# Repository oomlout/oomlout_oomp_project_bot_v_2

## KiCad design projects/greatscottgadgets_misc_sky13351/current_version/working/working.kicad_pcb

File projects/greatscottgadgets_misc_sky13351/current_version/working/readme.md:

# misc
 
## summary 
* id: greatscottgadgets_misc_sky13351
* user: greatscottgadgets
* name: misc
* board: sky13351
* repo: https://github.com/greatscottgadgets/misc
* src_file_repo_kicad_pcb: evaluation-boards/sky13351/sky13351.kicad_pcb
* src_file_repo_kicad_pcb_link: https://github.com/greatscottgadgets/misc/tree/master/evaluation-boards/sky13351/sky13351.kicad_pcb
* src_file_repo_kicad_sch: evaluation-boards/Si5351A/Si5351A.kicad_sch
* src_file_repo_kicad_sch_link: https://github.com/greatscottgadgets/misc/tree/master/evaluation-boards/Si5351A/Si5351A.kicad_sch

* src_file_repo_sch: evaluation-boards/sky13351/sky13351.sch
* src_file_repo_sch_link: https://github.com/greatscottgadgets/misc/tree/master/evaluation-boards/sky13351/sky13351.sch
* full details link: https://github.com/oomlout/oomlout_oomp_project_bot_v_2/tree/main/projects/greatscottgadgets_misc_sky13351/current_version/working

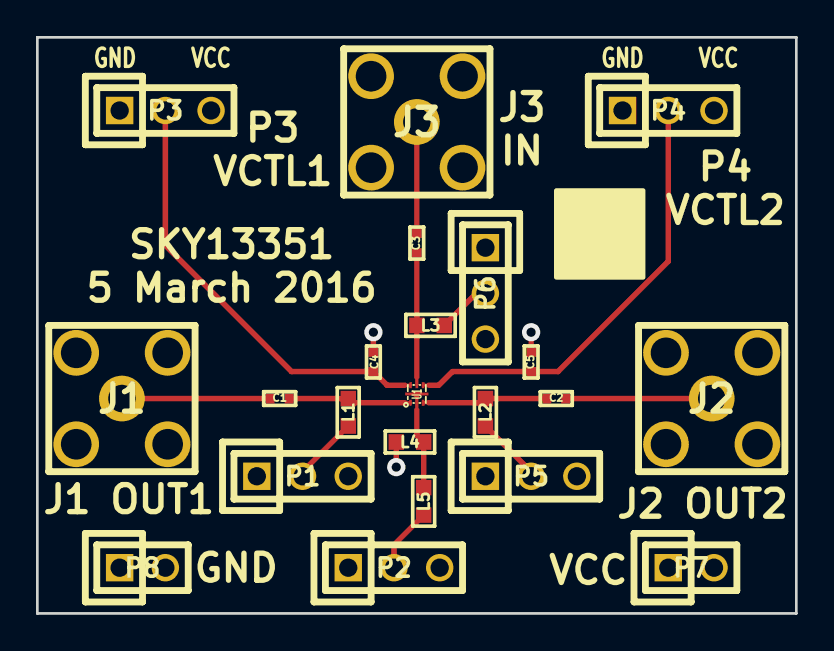
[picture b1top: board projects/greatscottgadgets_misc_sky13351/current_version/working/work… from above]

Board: 4 copper layers, 42.2 x 32.0 mm, 22 parts (0 on the bottom side), 15 nets.

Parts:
C1, C2, C3: 100nF; 0402
C4, C5: 33pF; 0402
J1, J2, J3: SMA; SMA-VERTICAL
L1, L2, L3, L4, L5: 15uH; 0603
P1, P2, P3, P4, P5, P6: CONN_01X03; HEADER-1x3
P7, P8: CONN_01X02; HEADER-1x2
U1: SKY13351; SKY13351-378LF

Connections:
GND: C4.2, C5.1, J1.2, J2.2, J3.2, L4.1, P1.1, P2.1, P3.1, P4.1, P5.1, P6.1, P8.1, P8.2
unnamed: C1.1, L1.2, U1.1
unnamed: C1.2, J1.1
unnamed: C2.1, J2.1
unnamed: C2.2, L2.2, U1.3
unnamed: C3.1, J3.1
unnamed: C3.2, L3.2, U1.5
unnamed: C4.1, P3.2, U1.6
unnamed: C5.2, P4.2, U1.4
unnamed: L1.1, P1.2
unnamed: L2.1, P5.2
unnamed: L3.1, P6.2
unnamed: L4.2, L5.2, U1.2
unnamed: L5.1, P2.2
VCC: P1.3, P2.3, P3.3, P4.3, P5.3, P6.3, P7.1, P7.2

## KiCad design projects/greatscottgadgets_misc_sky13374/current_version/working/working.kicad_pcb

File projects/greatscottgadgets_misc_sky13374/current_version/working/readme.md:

# misc
 
## summary 
* id: greatscottgadgets_misc_sky13374
* user: greatscottgadgets
* name: misc
* board: sky13374
* repo: https://github.com/greatscottgadgets/misc
* src_file_repo_kicad_pcb: evaluation-boards/sky13374/sky13374.kicad_pcb
* src_file_repo_kicad_pcb_link: https://github.com/greatscottgadgets/misc/tree/master/evaluation-boards/sky13374/sky13374.kicad_pcb
* src_file_repo_kicad_sch: evaluation-boards/Si5351A/Si5351A.kicad_sch
* src_file_repo_kicad_sch_link: https://github.com/greatscottgadgets/misc/tree/master/evaluation-boards/Si5351A/Si5351A.kicad_sch

* src_file_repo_sch: evaluation-boards/sky13374/sky13374.sch
* src_file_repo_sch_link: https://github.com/greatscottgadgets/misc/tree/master/evaluation-boards/sky13374/sky13374.sch
* full details link: https://github.com/oomlout/oomlout_oomp_project_bot_v_2/tree/main/projects/greatscottgadgets_misc_sky13374/current_version/working

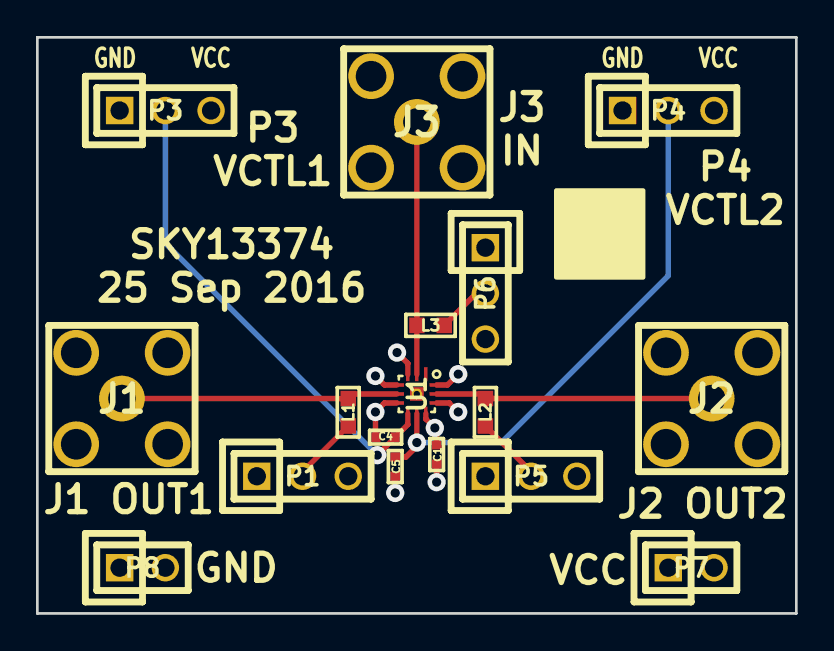
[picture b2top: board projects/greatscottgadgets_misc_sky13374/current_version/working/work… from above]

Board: 4 copper layers, 42.2 x 32.0 mm, 17 parts (0 on the bottom side), 10 nets.

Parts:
C1: 100nF; 0402
C4, C5: 33pF; 0402
J1, J2, J3: SMA; SMA-VERTICAL
L1, L2, L3: 15uH; 0603
P1, P3, P4, P5, P6: CONN_01X03; HEADER-1x3
P7, P8: CONN_01X02; HEADER-1x2
U1: SKY13374; SKY13374-397LF

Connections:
GND: C1.1, C4.2, C5.1, J1.2, J2.2, J3.2, P1.1, P3.1, P4.1, P5.1, P6.1, P8.1, P8.2, U1.0, U1.3, U1.4, U1.6, U1.10, U1.12
unnamed: C4.1, P3.2, U1.7
unnamed: C5.2, P4.2, U1.8
unnamed: J1.1, L1.2, U1.5
unnamed: J2.1, L2.2, U1.11
unnamed: J3.1, L3.2, U1.2
unnamed: L1.1, P1.2
unnamed: L2.1, P5.2
unnamed: L3.1, P6.2
VCC: C1.2, P1.3, P3.3, P4.3, P5.3, P6.3, P7.1, P7.2, U1.9

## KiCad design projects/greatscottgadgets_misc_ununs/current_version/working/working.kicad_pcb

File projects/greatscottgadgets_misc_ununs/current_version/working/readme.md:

# misc
 
## summary 
* id: greatscottgadgets_misc_ununs
* user: greatscottgadgets
* name: misc
* board: ununs
* repo: https://github.com/greatscottgadgets/misc
* src_file_repo_kicad_pcb: evaluation-boards/ununs/ununs.kicad_pcb
* src_file_repo_kicad_pcb_link: https://github.com/greatscottgadgets/misc/tree/master/evaluation-boards/ununs/ununs.kicad_pcb
* src_file_repo_kicad_sch: evaluation-boards/ununs/ununs.kicad_sch
* src_file_repo_kicad_sch_link: https://github.com/greatscottgadgets/misc/tree/master/evaluation-boards/ununs/ununs.kicad_sch

* src_file_repo_sch: evaluation-boards/ununs/ununs.sch
* src_file_repo_sch_link: https://github.com/greatscottgadgets/misc/tree/master/evaluation-boards/ununs/ununs.sch
* full details link: https://github.com/oomlout/oomlout_oomp_project_bot_v_2/tree/main/projects/greatscottgadgets_misc_ununs/current_version/working

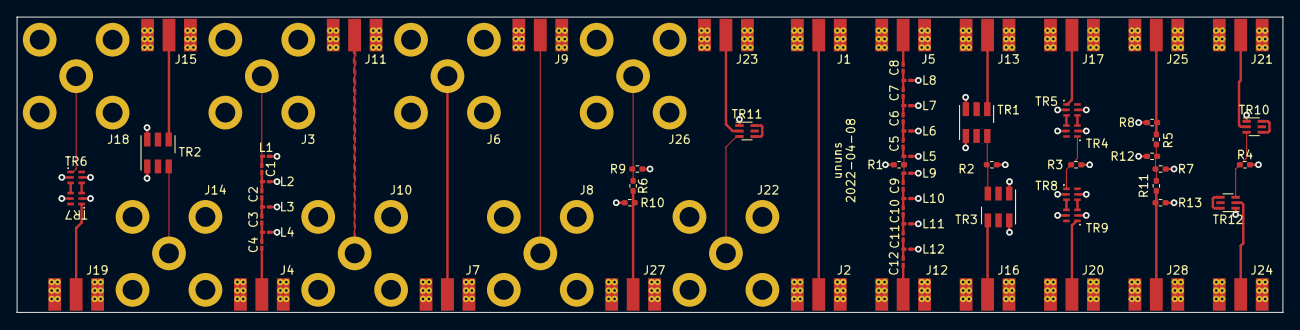
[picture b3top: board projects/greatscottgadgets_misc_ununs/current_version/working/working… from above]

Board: 4 copper layers, 150.0 x 35.0 mm, 77 parts (0 on the bottom side), 48 nets.

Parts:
C1, C5, C9: 3.9 pF; C_0201_0603Metric_Pad0.64x0.40mm_HandSolder
C2, C6, C10: 3.3 pF; C_0201_0603Metric_Pad0.64x0.40mm_HandSolder
C3, C7, C11: 15 pF; C_0201_0603Metric_Pad0.64x0.40mm_HandSolder
C4, C8, C12: 5.1 pF; C_0201_0603Metric_Pad0.64x0.40mm_HandSolder
J1, J2, J4, J5, J7, J9, J11, J12, J13, J15, J16, J17, J19, J20, J21, J23, J24, J25, J27, J28: Conn_Coaxial; SMA-EDGE
J3, J6, J8, J10, J14, J18, J22, J26: Conn_Coaxial; F_Cinch_VF320_Vertical
L1, L5, L9: 16 nH; L_0201_0603Metric_Pad0.64x0.40mm_HandSolder
L2, L6, L10: 20 nH; L_0201_0603Metric_Pad0.64x0.40mm_HandSolder
L3, L7, L11: 12 nH; L_0201_0603Metric_Pad0.64x0.40mm_HandSolder
L4, L8, L12: 22 nH; L_0201_0603Metric_Pad0.64x0.40mm_HandSolder
R1, R2, R3, R4: 75; R_0402_1005Metric_Pad0.72x0.64mm_HandSolder
R5, R6, R11: 43.2; R_0402_1005Metric_Pad0.72x0.64mm_HandSolder
R7, R9, R12: R; R_0402_1005Metric_Pad0.72x0.64mm_HandSolder
R8, R10, R13: 86.6; R_0402_1005Metric_Pad0.72x0.64mm_HandSolder
TR1, TR2, TR3: TC1.5-1+; Mini-Circuits_DB1627
TR4, TR6, TR8: HHM15112A1
TR5, TR7, TR9: 1720BL15A0100E; HHM15112A1
TR10, TR11, TR12: 1350BL15B0075; Balun_Johanson_0896BM15A0001

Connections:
GND: J1.2 (Ext), J2.2 (Ext), J3.2 (Ext), J4.2 (Ext), J5.2 (Ext), J6.2 (Ext), J7.2 (Ext), J8.2 (Ext), J9.2 (Ext), J10.2 (Ext), J11.2 (Ext), J12.2 (Ext), J13.2 (Ext), J14.2 (Ext), J15.2 (Ext), J16.2 (Ext), J17.2 (Ext), J18.2 (Ext), J19.2 (Ext), J20.2 (Ext), J21.2 (Ext), J22.2 (Ext), J23.2 (Ext), J24.2 (Ext), J25.2 (Ext), J26.2 (Ext), J27.2 (Ext), J28.2 (Ext), L1.2, L2.2, L3.2, L4.2, L5.2, L6.2, L7.2, L8.2, L9.2, L10.2, L11.2, L12.2, R1.2, R2.2, R3.2, R4.2, R7.2, R8.1, R9.2, R10.1, R12.2, R13.1, TR1.3, TR1.4, TR2.3, TR2.4, TR3.3, TR3.4, TR4.2, TR4.5, TR5.2, TR5.5, TR6.2, TR6.5, TR7.2, TR7.5, TR8.2, TR8.5, TR9.2, TR9.5, TR10.1, TR11.1, TR12.1
unnamed: C1.1, J3.1 (In), L1.1
unnamed: C1.2, C2.1, L2.1
unnamed: C2.2, C3.1, L3.1
unnamed: C3.2, C4.1, L4.1
unnamed: C4.2, J4.1 (In)
unnamed: C5.1, C9.1, L5.1, L9.1, R1.1
unnamed: C5.2, C6.1, L6.1
unnamed: C6.2, C7.1, L7.1
unnamed: C7.2, C8.1, L8.1
unnamed: C8.2, J5.1 (In)
unnamed: C9.2, C10.1, L10.1
unnamed: C10.2, C11.1, L11.1
unnamed: C11.2, C12.1, L12.1
unnamed: C12.2, J12.1 (In)
unnamed: J1.1 (In), J2.1 (In)
unnamed: J6.1 (In), J7.1 (In)
unnamed: J8.1 (In), J9.1 (In)
unnamed: J10.1 (In), J11.1 (In)
unnamed: J13.1 (In), TR1.6
unnamed: J14.1 (In), TR2.1
unnamed: J15.1 (In), TR2.6
unnamed: J16.1 (In), TR3.6
unnamed: J17.1 (In), TR5.1
unnamed: J18.1 (In), TR6.1
unnamed: J19.1 (In), TR7.1
unnamed: J20.1 (In), TR9.1
unnamed: J21.1 (In), TR10.2
unnamed: J22.1 (In), TR11.3
unnamed: J23.1 (In), TR11.2
unnamed: J24.1 (In), TR12.2
unnamed: J25.1 (In), R5.2, R8.2
unnamed: J26.1 (In), R6.1, R9.1
unnamed: J27.1 (In), R6.2, R10.2
unnamed: J28.1 (In), R11.2, R13.2
unnamed: R2.1, TR1.1, TR3.1
unnamed: R3.1, TR4.1, TR8.1
unnamed: R4.1, TR10.3, TR12.3
unnamed: R5.1, R7.1, R11.1, R12.1
unnamed: TR4.3, TR5.4
unnamed: TR4.4, TR5.3
unnamed: TR6.3, TR7.4
unnamed: TR6.4, TR7.3
unnamed: TR8.3, TR9.4
unnamed: TR8.4, TR9.3
unnamed: TR10.4, TR10.6
unnamed: TR11.4, TR11.6
unnamed: TR12.4, TR12.6

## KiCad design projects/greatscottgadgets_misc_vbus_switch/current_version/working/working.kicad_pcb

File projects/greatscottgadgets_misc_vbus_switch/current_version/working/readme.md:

# misc
 
## summary 
* id: greatscottgadgets_misc_vbus_switch
* user: greatscottgadgets
* name: misc
* board: vbus_switch
* repo: https://github.com/greatscottgadgets/misc
* src_file_repo_kicad_pcb: evaluation-boards/vbus-switch/vbus-switch.kicad_pcb
* src_file_repo_kicad_pcb_link: https://github.com/greatscottgadgets/misc/tree/master/evaluation-boards/vbus-switch/vbus-switch.kicad_pcb
* src_file_repo_kicad_sch: evaluation-boards/vbus-switch/vbus-switch.kicad_sch
* src_file_repo_kicad_sch_link: https://github.com/greatscottgadgets/misc/tree/master/evaluation-boards/vbus-switch/vbus-switch.kicad_sch

* src_file_repo_sch: evaluation-boards/ununs/ununs.sch
* src_file_repo_sch_link: https://github.com/greatscottgadgets/misc/tree/master/evaluation-boards/ununs/ununs.sch
* full details link: https://github.com/oomlout/oomlout_oomp_project_bot_v_2/tree/main/projects/greatscottgadgets_misc_vbus_switch/current_version/working

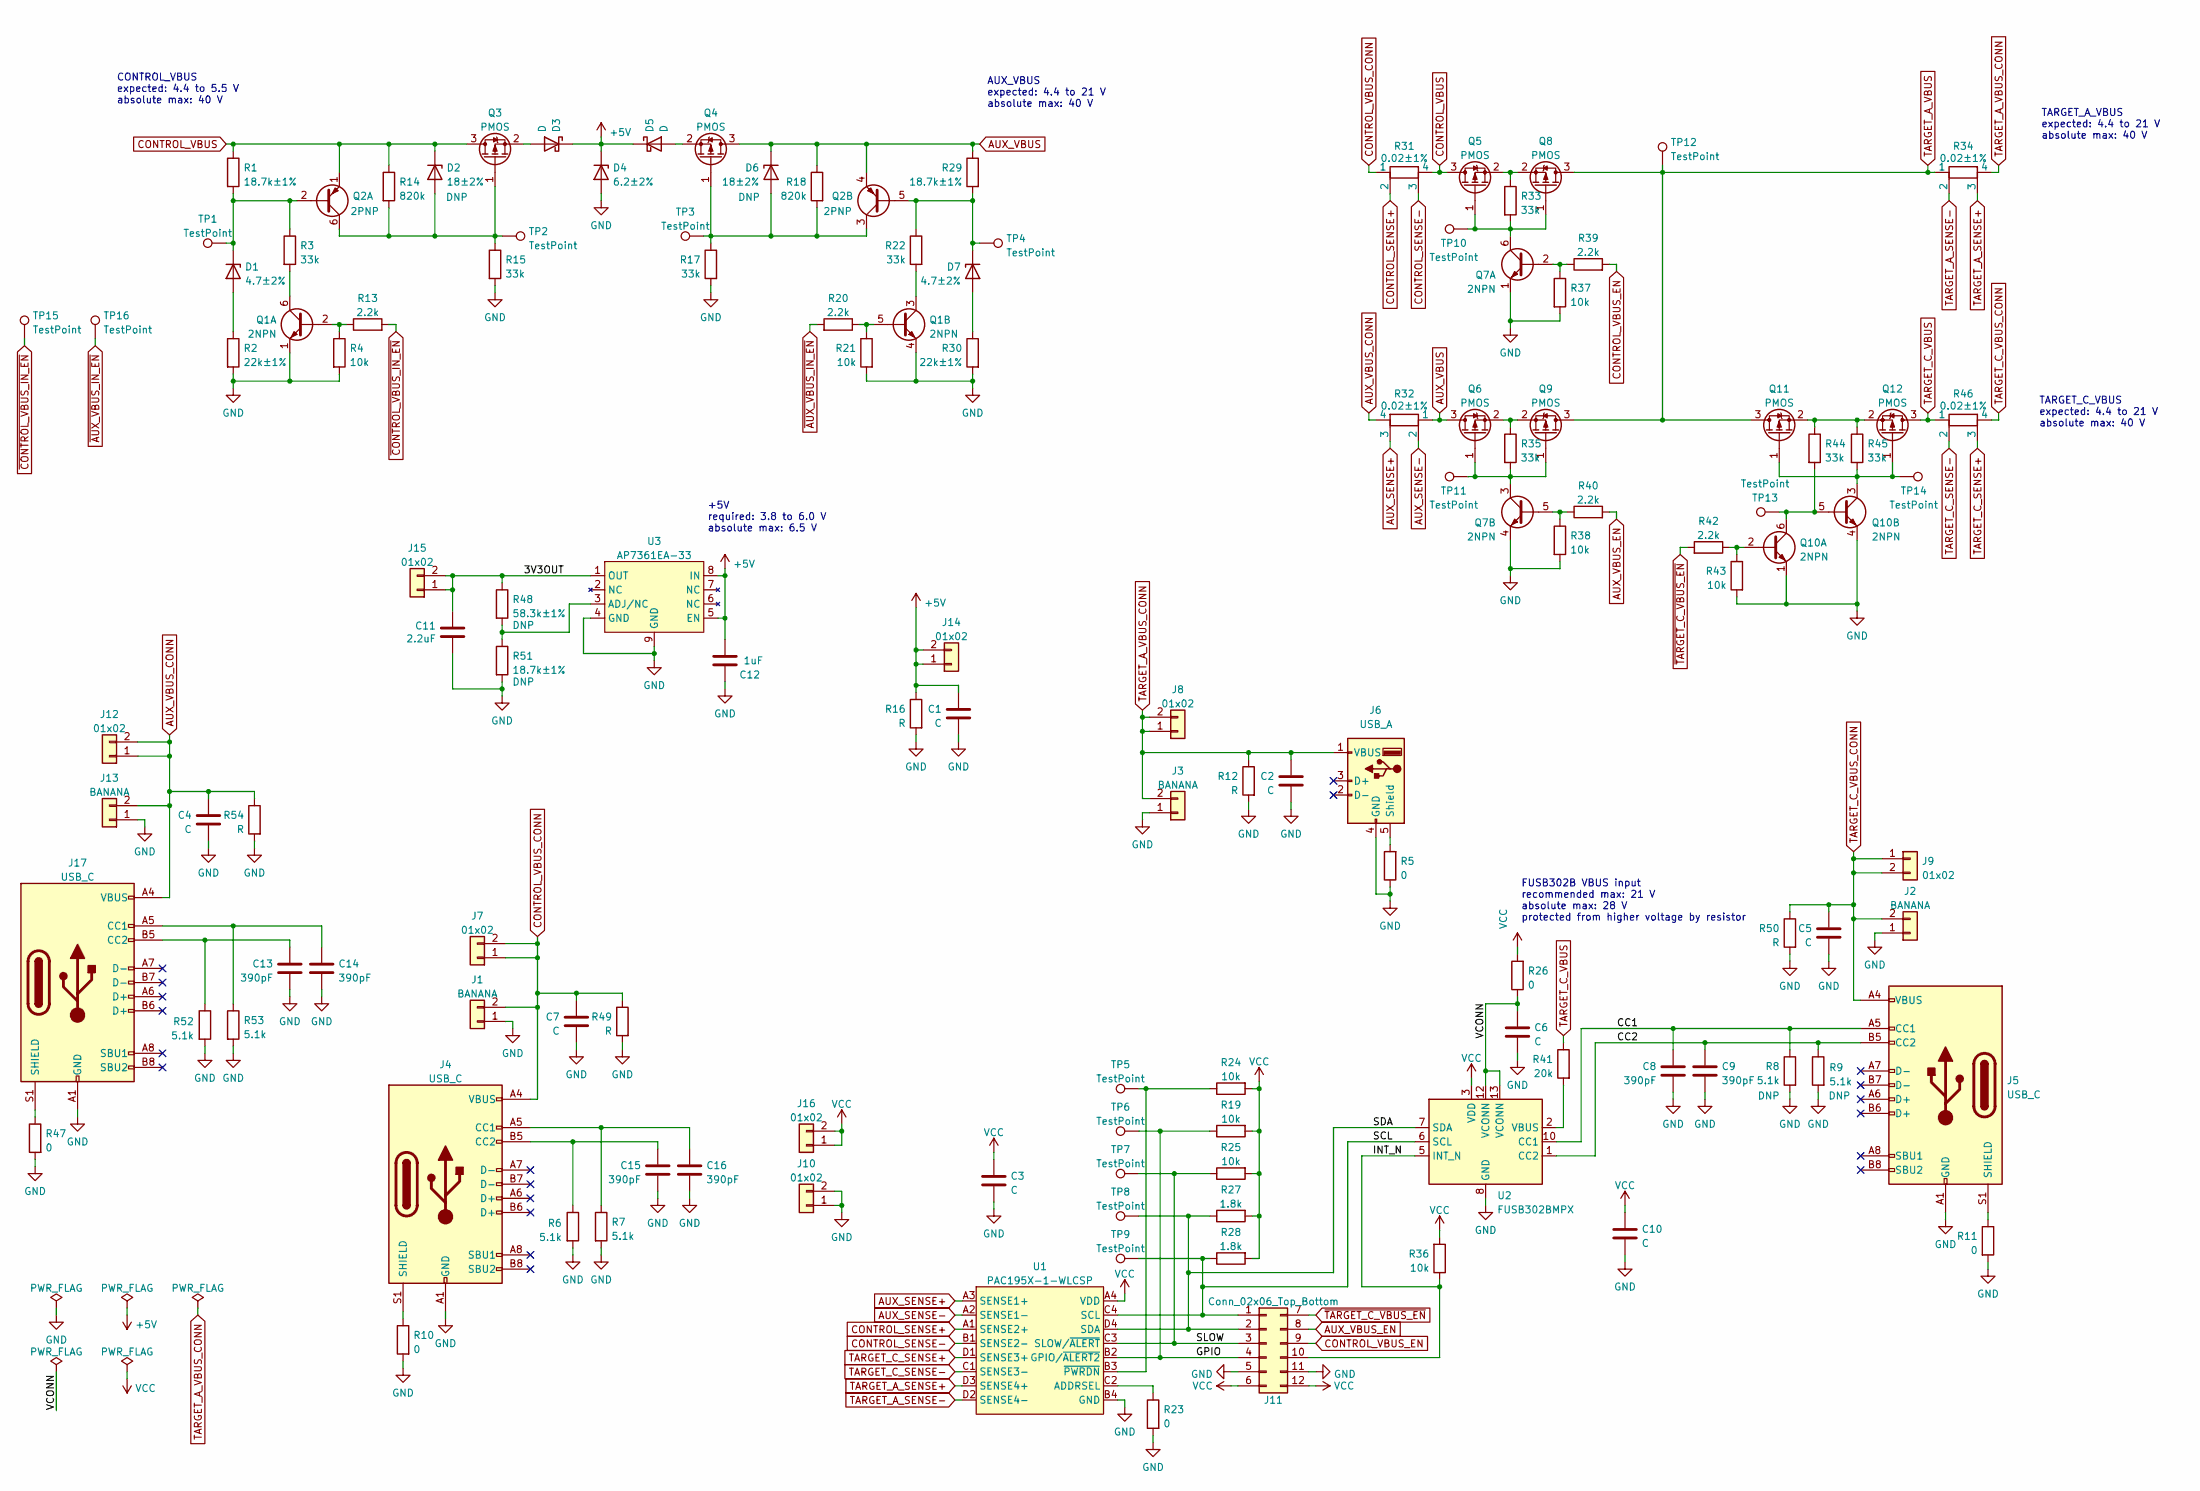
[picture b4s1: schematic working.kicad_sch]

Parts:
C1, C2, C3, C4, C5, C6, C7, C10: C; C_0402_1005Metric
C8, C9, C13, C14, C15, C16: 390pF; C_0402_1005Metric
C11: 2.2uF; C_0603_1608Metric; Part Number CL10A225KP8NNNC
C12: 1uF; C_0603_1608Metric; Part Number GENERIC-CAP-0603-1uF
D1, D7: 4.7±2%; DFN1006-2; Part Number BZX884-B4V7,315
D2, D6: 18±2%; DFN1006-2; Part Number BZX884-B18,315
D3, D5: D; D_SOD-123F; Part Number PMEG10010ELRX
D4: 6.2±2%; DFN1006-2; Part Number BZX884-B6V2,315
J1, J2, J3, J13: BANANA; Banana_Jack_2Pin
J4, J5, J17: USB_C; USB_C_Receptacle_HRO_TYPE-C-31-M-12; Part Number U262-161N-4BVC11
J6: USB_A; USB_A_Kycon_KUSBXHT-SB-AS1N-B30-NF_Horizontal; Part Number C42411
J7, J8, J9, J10, J12, J14, J15, J16: 01x02; PinHeader_1x02_P2.54mm_Vertical
J11: Conn_02x06_Top_Bottom; PinHeader_2x06_P2.54mm_PMOD
Q1, Q7, Q10: 2NPN; SOT-363_SC-70-6; Part Number BC847BS
Q2: 2PNP; SOT-363_SC-70-6; Part Number BCM857BS
Q3, Q4, Q5, Q6, Q8, Q9, Q11, Q12: PMOS; SOT-23-3; Part Number PJA3441_R1_00001
R1, R29, R51: 18.7k±1%; R_0402_1005Metric
R2, R30: 22k±1%; R_0402_1005Metric
R3, R15, R17, R22, R33, R35, R44, R45: 33k; R_0402_1005Metric
R4, R19, R21, R24, R25, R36, R37, R38, R43: 10k; R_0402_1005Metric
R5, R10, R11, R23, R26, R47: 0; R_0402_1005Metric
R6, R7, R8, R9, R52, R53: 5.1k; R_0402_1005Metric
R12, R16, R49, R50, R54: R; R_0402_1005Metric
R13, R20, R39, R40, R42: 2.2k; R_0402_1005Metric
R14, R18: 820k; R_0402_1005Metric
R27, R28: 1.8k; R_0402_1005Metric
R31, R32, R34, R46: 0.02±1%; R_0603_1608Metric_Current_Sense; Part Number ERJ-3BWFR020V
R41: 20k; R_0402_1005Metric
R48: 58.3k±1%; R_0402_1005Metric
TP1, TP2, TP3, TP4, TP5, TP6, TP7, TP8, TP9, TP10, TP11, TP12, TP13, TP14, TP15, TP16: TestPoint; TestPoint_Pad_D1.5mm
U1: PAC195X-1-WLCSP; WLCSP-16_2.225x2.170mm_Layout4x4_P0.5mm; Part Number PAC1954T-E/J6CX
U2: FUSB302BMPX; WQFN-14-1EP_2.5x2.5mm_P0.5mm_EP1.45x1.45mm; Part Number FUSB302BMPX
U3: AP7361EA-33; DFN-8-1EP_3x3mm_P0.65mm_EP1.55x2.4mm; Part Number AP7361EA-33FGE-7

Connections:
+5V: C1.1, C12.2, D3.1 (K), D4.1 (K), D5.1 (K), J14.1, J14.2, R16.1, U3.5 (EN), U3.8 (IN)
/3V3OUT: C11.1, J15.1, J15.2, R48.1, U3.1 (OUT)
/CC1: C8.2, J5.A5 (CC1), R8.1, U2.10 (CC1), U2.11 (CC1)
/CC2: C9.1, J5.B5 (CC2), R9.1, U2.1 (CC2), U2.14 (CC2)
/GPIO: J11.4, R19.1, TP6.1, U1.B2 (GPIO/~ALERT2)
/INT_N: J11.10, R36.1, U2.5 (INT_N)
/SCL: J11.1, R28.1, TP9.1, U1.C4 (SCL), U2.6 (SCL)
/SDA: J11.2, R27.1, TP8.1, U1.D4 (SDA), U2.7 (SDA)
/SLOW: J11.3, R25.1, TP7.1, U1.C3 (SLOW/~ALERT)
/VCONN: C6.1, R26.1, U2.12 (VCONN), U2.13 (VCONN)
AUX_SENSE+: R32.3, U1.A3 (SENSE1+)
AUX_SENSE-: R32.2, U1.A2 (SENSE1-)
AUX_VBUS: D6.1 (K), Q2.4 (E2), Q4.3 (D), Q6.3 (D), R18.1, R29.1, R32.1
AUX_VBUS_CONN: C4.1, J12.1, J12.2, J13.2, J17.A4 (VBUS), J17.A9 (VBUS), J17.B4 (VBUS), J17.B9 (VBUS), R32.4, R54.1
AUX_VBUS_EN: J11.8, R40.2
CONTROL_SENSE+: R31.2, U1.A1 (SENSE2+)
CONTROL_SENSE-: R31.3, U1.B1 (SENSE2-)
CONTROL_VBUS: D2.1 (K), Q2.1 (E1), Q3.3 (D), Q5.3 (D), R1.1, R14.1, R31.4
CONTROL_VBUS_CONN: C7.1, J1.2, J4.A4 (VBUS), J4.A9 (VBUS), J4.B4 (VBUS), J4.B9 (VBUS), J7.1, J7.2, R31.1, R49.1
CONTROL_VBUS_EN: J11.9, R39.2
GND: C1.2, C2.2, C3.2, C4.2, C5.2, C6.2, C7.2, C8.1, C9.2, C10.2, C11.2, C12.1, C13.1, C14.2, C15.1, C16.2, D4.2 (A), J1.1, J2.1, J3.1, J4.A1 (GND), J4.A12 (GND), J4.B1 (GND), J4.B12 (GND), J5.A1 (GND), J5.A12 (GND), J5.B1 (GND), J5.B12 (GND), J6.4 (GND), J10.1, J10.2, J11.5, J11.11, J13.1, J17.A1 (GND), J17.A12 (GND), J17.B1 (GND), J17.B12 (GND), Q1.1 (E1), Q1.4 (E2), Q7.1 (E1), Q7.4 (E2), Q10.1 (E1), Q10.4 (E2), R2.2, R4.2, R5.1, R6.2, R7.2, R8.2, R9.2, R10.2, R11.2, R12.2, R15.2, R16.2, R17.2, R21.2, R23.2, R30.2, R37.2, R38.2, R43.2, R47.2, R49.2, R50.2, R51.2, R52.2, R53.2, R54.2, U1.B4 (GND), U2.8 (GND), U2.9 (GND), U2.15 (GND), U3.4 (GND), U3.9 (GND)
unnamed: C13.2, J17.B5 (CC2), R52.1
unnamed: C14.1, J17.A5 (CC1), R53.1
unnamed: C15.2, J4.B5 (CC2), R6.1
unnamed: C16.1, J4.A5 (CC1), R7.1
unnamed: D1.1 (K), Q2.2 (B1), R1.2, R3.1, TP1.1
unnamed: D1.2 (A), R2.1
unnamed: D2.2 (A), Q2.6 (C1), Q3.1 (G), R14.2, R15.1, TP2.1
unnamed: D3.2 (A), Q3.2 (S)
unnamed: D5.2 (A), Q4.2 (S)
unnamed: D6.2 (A), Q2.3 (C2), Q4.1 (G), R17.1, R18.2, TP3.1
unnamed: D7.1 (K), Q2.5 (B2), R22.1, R29.2, TP4.1
unnamed: D7.2 (A), R30.1
unnamed: J4.S1 (SHIELD), R10.1
unnamed: J5.S1 (SHIELD), R11.1
unnamed: J6.5 (Shield), R5.2
unnamed: J17.S1 (SHIELD), R47.1
unnamed: Q1.2 (B1), R4.1, R13.1
unnamed: Q1.3 (C2), R22.2
unnamed: Q1.5 (B2), R20.1, R21.1
unnamed: Q1.6 (C1), R3.2
unnamed: Q5.1 (G), Q7.6 (C1), Q8.1 (G), R33.2, TP10.1
unnamed: Q5.2 (S), Q8.2 (S), R33.1
unnamed: Q6.1 (G), Q7.3 (C2), Q9.1 (G), R35.2, TP11.1
unnamed: Q6.2 (S), Q9.2 (S), R35.1
unnamed: Q7.2 (B1), R37.1, R39.1
unnamed: Q7.5 (B2), R38.1, R40.1
unnamed: Q10.2 (B1), R42.1, R43.1
unnamed: Q10.3 (C2), Q11.1 (G), Q12.1 (G), R45.2, TP14.1
unnamed: Q10.5 (B2), Q10.6 (C1), R44.2, TP13.1
unnamed: Q11.2 (S), Q12.2 (S), R44.1, R45.1
unnamed: R23.1, U1.C2 (ADDRSEL)
unnamed: R24.1, TP5.1, U1.B3 (~PWRDN)
unnamed: R41.2, U2.2 (VBUS)
unnamed: R48.2, R51.1, U3.3 (ADJ/NC)
TARGET_A_SENSE+: R34.3, U1.D3 (SENSE4+)
TARGET_A_SENSE-: R34.2, U1.D2 (SENSE4-)
TARGET_A_VBUS: Q8.3 (D), Q9.3 (D), Q11.3 (D), R34.1, TP12.1
TARGET_A_VBUS_CONN: C2.1, J3.2, J6.1 (VBUS), J8.1, J8.2, R12.1, R34.4
TARGET_C_SENSE+: R46.3, U1.D1 (SENSE3+)
TARGET_C_SENSE-: R46.2, U1.C1 (SENSE3-)
TARGET_C_VBUS: Q12.3 (D), R41.1, R46.1
TARGET_C_VBUS_CONN: C5.1, J2.2, J5.A4 (VBUS), J5.A9 (VBUS), J5.B4 (VBUS), J5.B9 (VBUS), J9.1, J9.2, R46.4, R50.1
VCC: C3.1, C10.1, J11.6, J11.12, J16.1, J16.2, R19.2, R24.2, R25.2, R26.2, R27.2, R28.2, R36.2, U1.A4 (VDD), U2.3 (VDD), U2.4 (VDD)
~AUX_VBUS_IN_EN: R20.2, TP16.1
~CONTROL_VBUS_IN_EN: R13.2, TP15.1
~TARGET_C_VBUS_EN: J11.7, R42.2

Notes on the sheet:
CONTROL_VBUS expected: 4.4 to 5.5 V absolute max: 40 V
+5V required: 3.8 to 6.0 V absolute max: 6.5 V
AUX_VBUS expected: 4.4 to 21 V absolute max: 40 V
FUSB302B VBUS input recommended max: 21 V absolute max: 28 V protected from higher voltage by resistor
TARGET_C_VBUS expected: 4.4 to 21 V absolute max: 40 V
TARGET_A_VBUS expected: 4.4 to 21 V absolute max: 40 V

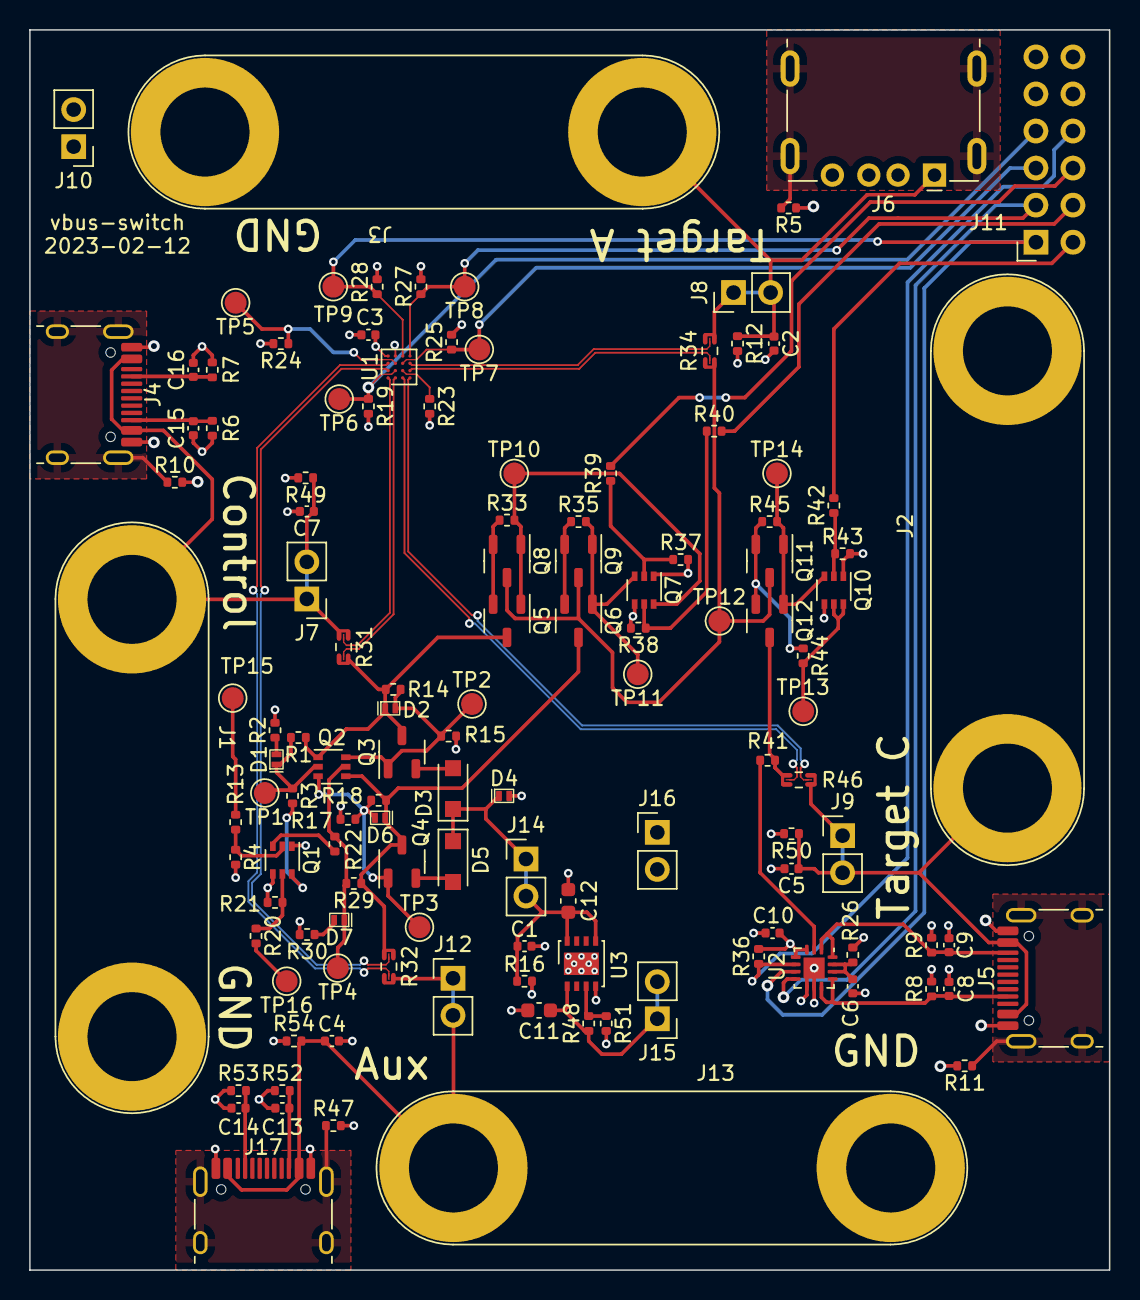
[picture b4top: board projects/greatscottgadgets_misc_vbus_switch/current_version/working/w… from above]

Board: 4 copper layers, 74.0 x 85.0 mm, 125 parts (0 on the bottom side), 67 nets.

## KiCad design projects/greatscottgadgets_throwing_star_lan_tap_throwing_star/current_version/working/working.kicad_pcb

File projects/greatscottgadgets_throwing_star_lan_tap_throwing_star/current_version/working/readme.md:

# throwing_star_lan_tap
 
## summary 
* id: greatscottgadgets_throwing_star_lan_tap_throwing_star
* user: greatscottgadgets
* name: throwing_star_lan_tap
* board: throwing_star
* repo: https://github.com/greatscottgadgets/throwing-star-lan-tap
* src_file_repo_kicad_pcb: throwing-star-pro.kicad_pcb
* src_file_repo_kicad_pcb_link: https://github.com/greatscottgadgets/throwing-star-lan-tap/tree/master/throwing-star-pro.kicad_pcb

* src_file_repo_sch: 
* src_file_repo_sch_link: https://github.com/greatscottgadgets/throwing-star-lan-tap/tree/master/
* full details link: https://github.com/oomlout/oomlout_oomp_project_bot_v_2/tree/main/projects/greatscottgadgets_throwing_star_lan_tap_throwing_star/current_version/working

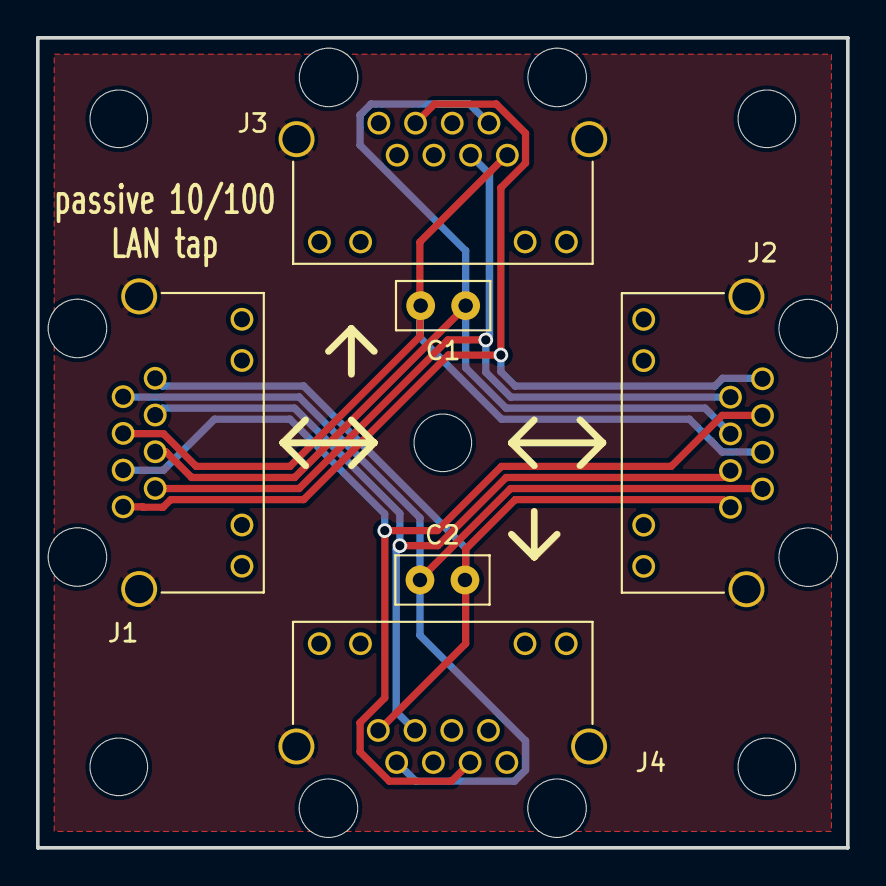
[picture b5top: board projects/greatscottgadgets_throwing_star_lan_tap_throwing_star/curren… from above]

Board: 2 copper layers, 45.0 x 45.0 mm, 6 parts (0 on the bottom side), 9 nets.

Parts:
C1, C2: 220pF; C_Disc_D5.0mm_W2.5mm_P2.50mm
J1, J2, J3, J4: RJ45_Shielded; RJ45_Amphenol_RJHSE538X_TSLTP

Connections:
/SIG1: J1.1, J2.1, J3.3
/SIG2: J1.2, J2.2, J3.6
/SIG3: J1.3, J2.3, J4.3
/SIG4: C1.1, J1.4, J2.4, J3.7
/SIG5: C1.2, J1.5, J2.5, J3.8
/SIG6: J1.6, J2.6, J4.6
/SIG7: C2.1, J1.7, J2.7, J4.7
/SIG8: C2.2, J1.8, J2.8, J4.8
GND: J1.SH, J2.SH, J3.SH, J4.SH

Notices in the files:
projects/greatscottgadgets_throwing_star_lan_tap_throwing_star/current_version/working/working.kicad_pcb:
Copyright (c) 2010-2020 Great Scott Gadgets
Licensed under the CERN-OHL-P v2
